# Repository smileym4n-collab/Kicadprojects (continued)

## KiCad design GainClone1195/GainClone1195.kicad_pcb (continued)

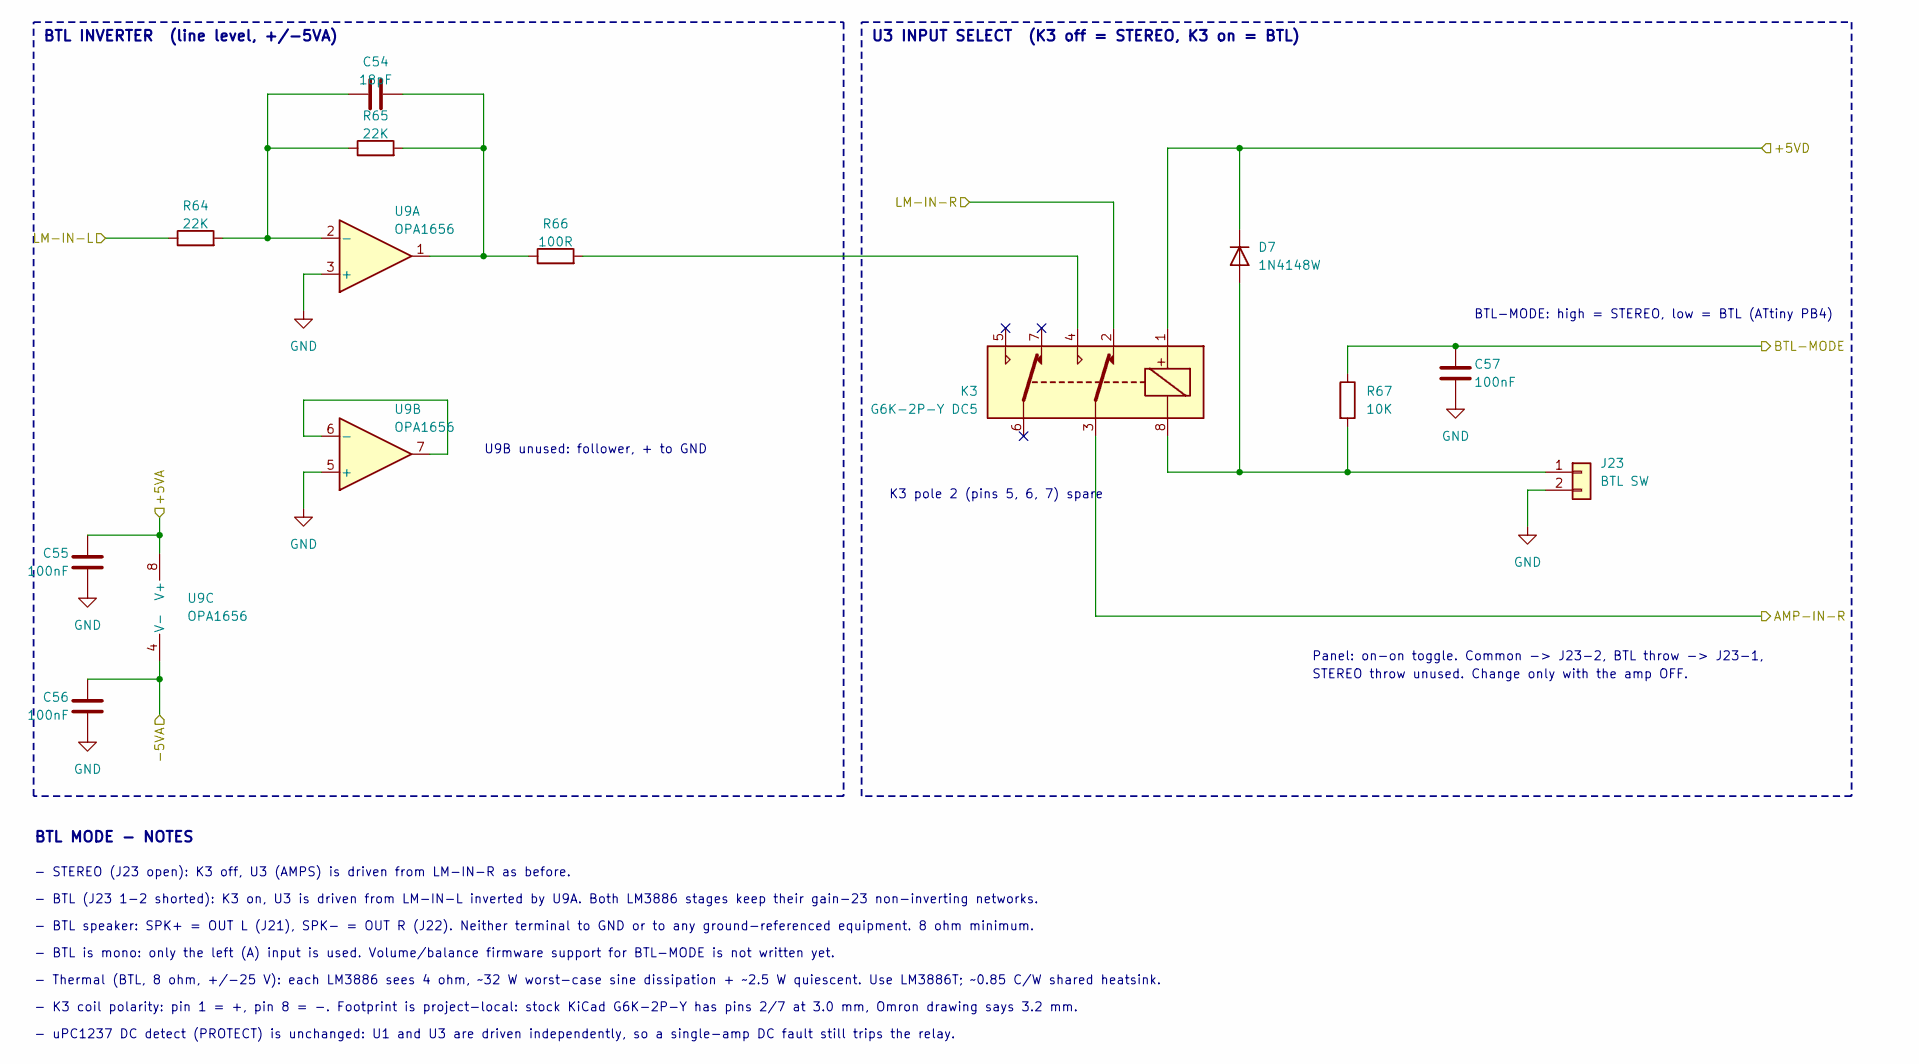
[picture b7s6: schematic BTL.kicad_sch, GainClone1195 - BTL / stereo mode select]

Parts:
C54: 18pF; C_0603_1608Metric_Pad1.08x0.95mm_HandSolder; MPN VJ0603A180JXACW1BC
C55, C56, C57: 100nF; C_0603_1608Metric_Pad1.08x0.95mm_HandSolder; MPN C0603C104M5RACTU
D7: 1N4148W; D_SOD-123; MPN 1N4148W
J23: BTL SW; JST_XH_B2B-XH-A_1x02_P2.50mm_Vertical; MPN B2B-XH-A
K3: G6K-2P-Y DC5; Relay_DPDT_Omron_G6K-2P-Y; MPN G6K-2P-Y DC5
R64, R65: 22K; R_0805_2012Metric_Pad1.20x1.40mm_HandSolder; MPN RR1220P-223-D
R66: 100R; R_0805_2012Metric_Pad1.20x1.40mm_HandSolder; MPN RC0805FR-07100RL
R67: 10K; R_0805_2012Metric_Pad1.20x1.40mm_HandSolder; MPN RC0805FR-0710KL
U9: OPA1656; SOIC-8_3.9x4.9mm_P1.27mm; MPN OPA1656IDR

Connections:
/+5VA: C55.1, U9.8 (V+); also elsewhere on the board
/+5VD: D7.1 (K), K3.1; also elsewhere on the board
/-5VA: C56.1, U9.4 (V-); also elsewhere on the board
/AMP-IN-R: K3.3; also elsewhere on the board
/BTL-MODE: C57.1, R67.1; also elsewhere on the board
/LM-IN-L: R64.1; also elsewhere on the board
/LM-IN-R: K3.2; also elsewhere on the board
GND: C55.2, C56.2, C57.2, J23.2, U9.3 (+), U9.5 (+); also elsewhere on the board
unnamed: C54.2, R65.2, R66.1, U9.1
unnamed: D7.2 (A), J23.1, K3.8, R67.2
unnamed: K3.4, R66.2
unnamed: C54.1, R64.2, R65.1, U9.2 (-)
unnamed: U9.6 (-), U9.7

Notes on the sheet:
- Thermal (BTL, 8 ohm, +/-25 V): each LM3886 sees 4 ohm, ~32 W worst-case sine dissipation + ~2.5 W quiescent. Use LM3886T; ~0.85 C/W shared heatsink.
Panel: on-on toggle. Common -> J23-2, BTL throw -> J23-1,
- K3 coil polarity: pin 1 = +, pin 8 = -. Footprint is project-local: stock KiCad G6K-2P-Y has pins 2/7 at 3.0 mm, Omron drawing says 3.2 mm.
U9B unused: follower, + to GND
BTL-MODE: high = STEREO, low = BTL (ATtiny PB4)
STEREO throw unused. Change only with the amp OFF.
- BTL speaker: SPK+ = OUT L (J21), SPK- = OUT R (J22). Neither terminal to GND or to any ground-referenced equipment. 8 ohm minimum.
K3 pole 2 (pins 5, 6, 7) spare
BTL INVERTER (line level, +/-5VA)
- STEREO (J23 open): K3 off, U3 (AMPS) is driven from LM-IN-R as before.
U3 INPUT SELECT (K3 off = STEREO, K3 on = BTL)
- BTL (J23 1-2 shorted): K3 on, U3 is driven from LM-IN-L inverted by U9A. Both LM3886 stages keep their gain-23 non-inverting networks.
- BTL is mono: only the left (A) input is used. Volume/balance firmware support for BTL-MODE is not written yet.
- uPC1237 DC detect (PROTECT) is unchanged: U1 and U3 are driven independently, so a single-amp DC fault still trips the relay.
BTL MODE - NOTES

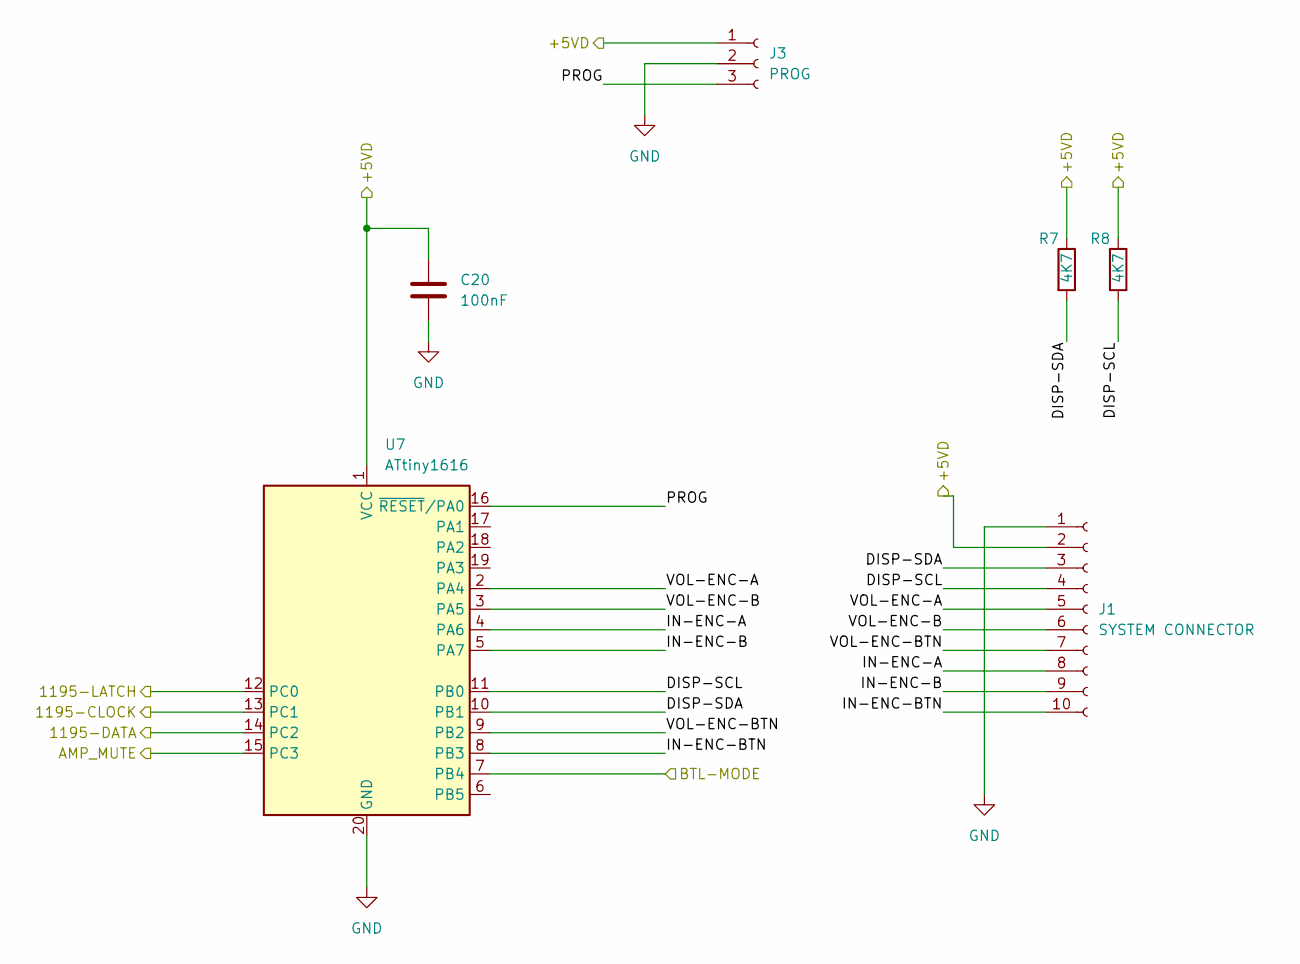
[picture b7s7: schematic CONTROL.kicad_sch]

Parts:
C20: 100nF; C_1206_3216Metric_Pad1.33x1.80mm_HandSolder
J1: SYSTEM CONNECTOR; JST_XH_B10B-XH-A_1x10_P2.50mm_Vertical
J3: PROG; PinHeader_1x03_P2.54mm_Vertical
R7, R8: 4K7; R_0805_2012Metric_Pad1.20x1.40mm_HandSolder
U7: ATtiny1616; SSOP-20_5.3x7.2mm_P0.65mm

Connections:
/+5VD: C20.1, J1.2, J3.1, R7.1, R8.1, U7.1 (VCC); also elsewhere on the board
/AMPS/AMP-MUTE: U7.15 (PC3); also elsewhere on the board
/BTL-MODE: U7.7 (PB4); also elsewhere on the board
/CONTROL/1195-CLOCK: U7.13 (PC1); also elsewhere on the board
/CONTROL/1195-DATA: U7.14 (PC2); also elsewhere on the board
/CONTROL/1195-LATCH: U7.12 (PC0); also elsewhere on the board
/CONTROL/DISP-SCL: J1.4, R8.2, U7.11 (PB0)
/CONTROL/DISP-SDA: J1.3, R7.2, U7.10 (PB1)
/CONTROL/IN-ENC-A: J1.8, U7.4 (PA6)
/CONTROL/IN-ENC-B: J1.9, U7.5 (PA7)
/CONTROL/IN-ENC-BTN: J1.10, U7.8 (PB3)
/CONTROL/PROG: J3.3, U7.16 (~RESET/PA0)
/CONTROL/VOL-ENC-A: J1.5, U7.2 (PA4)
/CONTROL/VOL-ENC-B: J1.6, U7.3 (PA5)
/CONTROL/VOL-ENC-BTN: J1.7, U7.9 (PB2)
GND: C20.2, J1.1, J3.2, U7.20 (GND); also elsewhere on the board

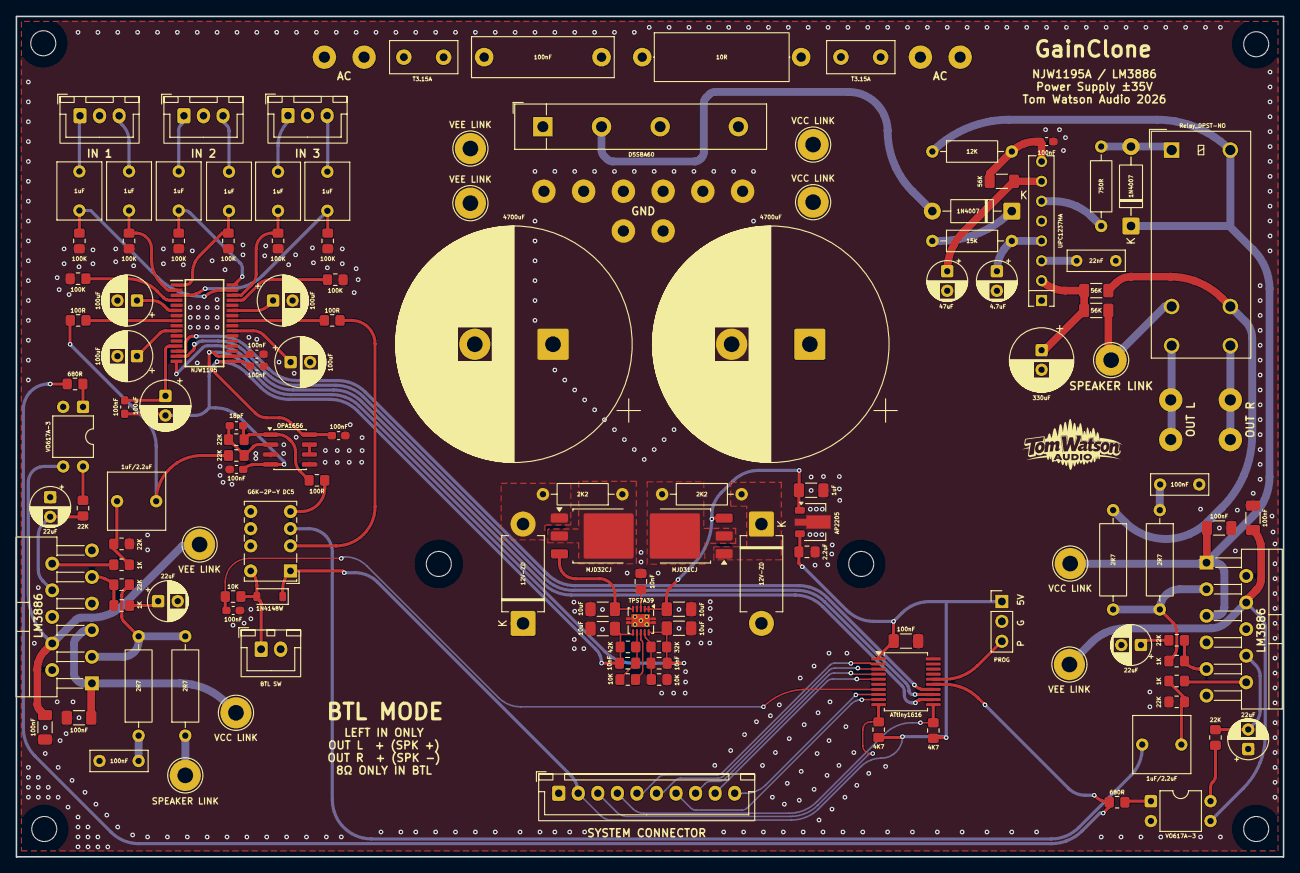
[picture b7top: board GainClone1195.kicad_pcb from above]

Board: 2 copper layers, 162.0 x 107.4 mm, 145 parts (0 on the bottom side), 97 nets.

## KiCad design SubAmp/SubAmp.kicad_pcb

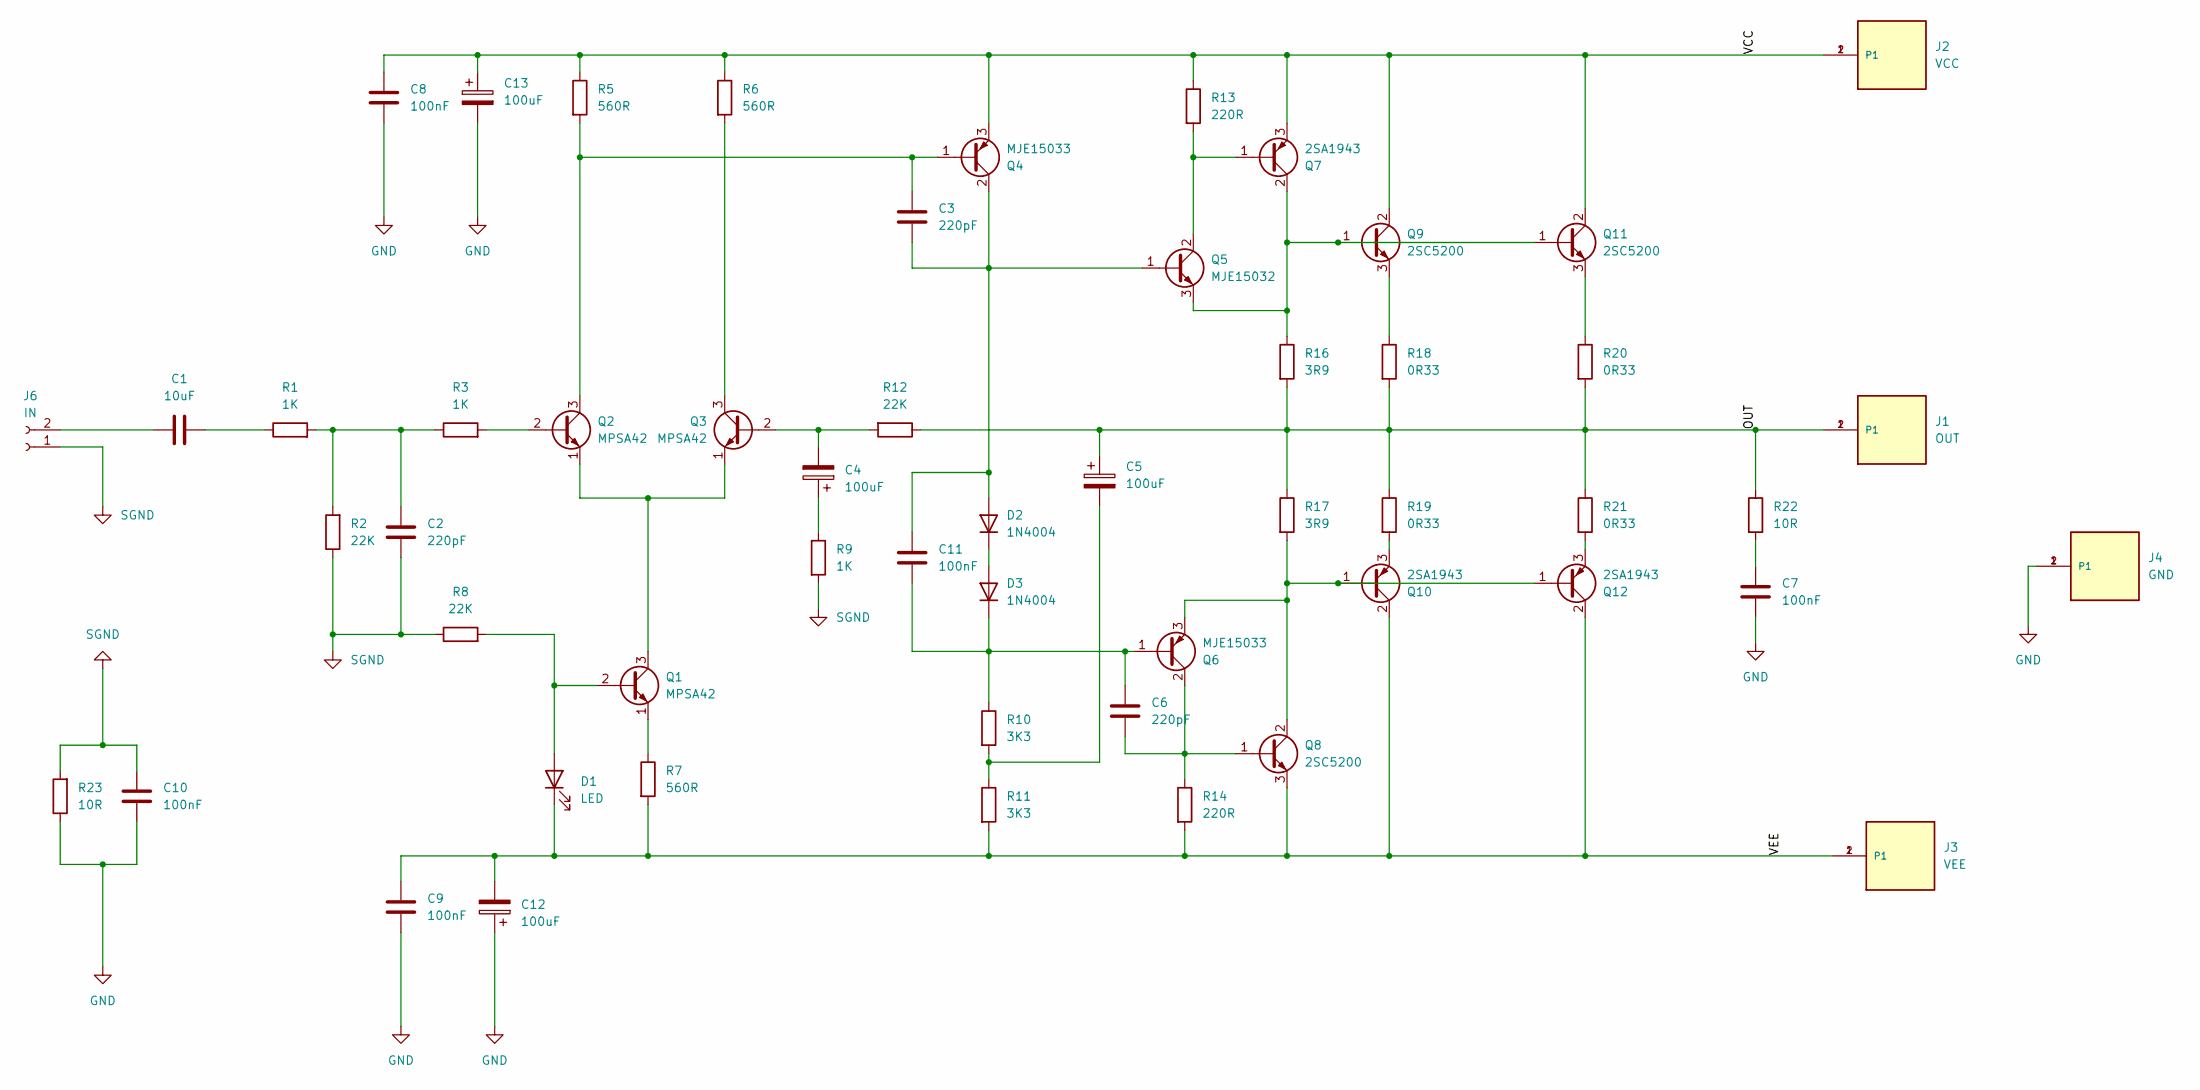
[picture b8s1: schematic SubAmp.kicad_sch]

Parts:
C1: 10uF; C_Radial_D8.0mm_H11.5mm_P3.50mm; Manufacturer_Part_Number UES1H100MPM
C2: 220pF; C_0805_2012Metric_Pad1.18x1.45mm_HandSolder; Manufacturer_Part_Number 220pfMLCCC0G50V2012
C3, C6: 220pF; C_0805_2012Metric_Pad1.18x1.45mm_HandSolder; Manufacturer_Part_Number C0805C221JAGACTU
C4: 100uF; CP_Radial_D5.0mm_P2.50mm; Manufacturer_Part_Number EEUFR1C101
C5: 100uF; CP_Radial_D8.0mm_P3.50mm; Manufacturer_Part_Number EEUFR1H101
C7: 100nF; C_Rect_L7.2mm_W2.5mm_P5.00mm_FKS2_FKP2_MKS2_MKP2; Manufacturer_Part_Number R82DC3100DQ50J
C8, C9: 100nF; C_1206_3216Metric_Pad1.33x1.80mm_HandSolder; Voltage_Rating 100; Manufacturer_Part_Number C1206C104K1RACTU
C10, C11: 100nF; C_Rect_L7.0mm_W2.5mm_P5.00mm; Manufacturer_Part_Number R82DC3100DQ50J
C12, C13: 100uF; CP_Radial_D10.0mm_P5.00mm; Manufacturer_Part_Number EEUFR2A101
D1: LED; LED_D5.0mm
D2, D3: 1N4004; D_DO-41_SOD81_P10.16mm_Horizontal; Manufacturer_Part_Number 1N4004
J1: OUT; TE_62409-1; PART_DESCRIPTION CONN QC TAB 0.250 SOLDER
J2: VCC; TE_62409-1; PART_DESCRIPTION CONN QC TAB 0.250 SOLDER
J3: VEE; TE_62409-1; PART_DESCRIPTION CONN QC TAB 0.250 SOLDER
J4: GND; TE_62409-1; PART_DESCRIPTION CONN QC TAB 0.250 SOLDER
J6: IN; JST_XH_B2B-XH-A_1x02_P2.50mm_Vertical; Manufacturer_Part_Number MC34629
Q1, Q2, Q3: MPSA42; TO-92_Wide; Manufacturer_Part_Number MPSA42
Q4, Q6: MJE15033; TO-220-3_Vertical; Manufacturer_Part_Number MJE15033G
Q5: MJE15032; TO-220-3_Vertical; Manufacturer_Part_Number MJE15032G
Q7, Q10, Q12: 2SA1943; TO-264-3_Horizontal_TabDown; Manufacturer_Part_Number 2SA1943
Q8, Q9, Q11: 2SC5200; TO-264-3_Horizontal_TabDown; Manufacturer_Part_Number 2SC5200
R1, R3, R9: 1K; R_Axial_DIN0207_L6.3mm_D2.5mm_P10.16mm_Horizontal; Manufacturer_Part_Number LR1F1K
R2, R8, R12: 22K; R_Axial_DIN0207_L6.3mm_D2.5mm_P10.16mm_Horizontal; Manufacturer_Part_Number LR1F22K
R5, R6, R7: 560R; R_Axial_DIN0207_L6.3mm_D2.5mm_P10.16mm_Horizontal; Manufacturer_Part_Number LR1F560R
R10, R11: 3K3; R_Axial_DIN0207_L6.3mm_D2.5mm_P10.16mm_Horizontal; Manufacturer_Part_Number LR1F3K3
R13, R14: 220R; R_Axial_DIN0207_L6.3mm_D2.5mm_P10.16mm_Horizontal; Manufacturer_Part_Number LR1F220R
R16, R17: 3R9; R_Axial_DIN0617_L17.0mm_D6.0mm_P25.40mm_Horizontal; Manufacturer_Part_Number Multicomp Pro
R18, R19, R20, R21: 0R33; R_Axial_DIN0617_L17.0mm_D6.0mm_P25.40mm_Horizontal; Manufacturer_Part_Number Multicomp Pro
R22, R23: 10R; R_Axial_DIN0414_L11.9mm_D4.5mm_P15.24mm_Horizontal; Manufacturer_Part_Number RSMF2JT10R0

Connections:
/OUT: C5.1, J1.1, J1.2 (P1), R12.1, R16.2, R17.1, R18.2, R19.1, R20.2, R21.1, R22.1
/VCC: C8.1, C13.1, J2.1, J2.2 (P1), Q4.3 (E), Q7.3 (E), Q9.2 (C), Q11.2 (C), R5.1, R6.1, R13.1
/VEE: C9.1, C12.2, D1.1 (K), J3.1, J3.2 (P1), Q8.3 (E), Q10.2 (C), Q12.2 (C), R7.2, R11.2, R14.2
GND: C7.2, C8.2, C9.2, C10.2, C12.1, C13.2, J4.1, J4.2 (P1), R23.1
unnamed: C1.2, R1.1
unnamed: C2.1, R1.2, R2.2, R3.1
unnamed: C4.1, R9.1
unnamed: C5.2, R10.2, R11.1
unnamed: C7.1, R22.2
unnamed: D1.2 (A), Q1.2 (B), R8.2
unnamed: C3.2, C11.1, D2.2 (A), Q4.2 (C), Q5.1 (B)
unnamed: D2.1 (K), D3.2 (A)
unnamed: C6.1, C11.2, D3.1 (K), Q6.1 (B), R10.1
unnamed: C1.1, J6.2
unnamed: Q1.3 (C), Q2.1 (E), Q3.1 (E)
unnamed: Q1.1 (E), R7.1
unnamed: Q2.2 (B), R3.2
unnamed: C3.1, Q2.3 (C), Q4.1 (B), R5.2
unnamed: C4.2, Q3.2 (B), R12.2
unnamed: Q3.3 (C), R6.2
unnamed: Q5.2 (C), Q7.1 (B), R13.2
unnamed: C6.2, Q6.2 (C), Q8.1 (B), R14.1
unnamed: Q9.3 (E), R18.1
unnamed: Q6.3 (E), Q8.2 (C), Q10.1 (B), Q12.1 (B), R17.2
unnamed: Q10.3 (E), R19.2
unnamed: Q5.3 (E), Q7.2 (C), Q9.1 (B), Q11.1 (B), R16.1
unnamed: Q11.3 (E), R20.1
unnamed: Q12.3 (E), R21.2
SGND: C2.2, C10.1, J6.1, R2.1, R8.1, R9.2, R23.2

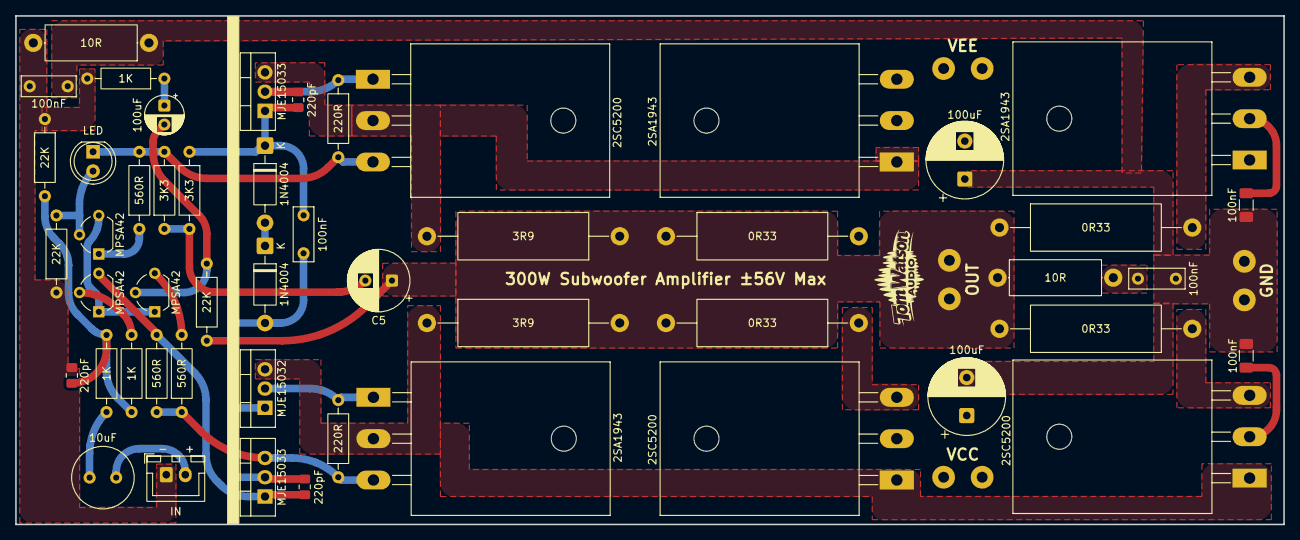
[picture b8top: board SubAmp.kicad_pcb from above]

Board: 2 copper layers, 167.1 x 67.0 mm, 54 parts (0 on the bottom side), 29 nets.

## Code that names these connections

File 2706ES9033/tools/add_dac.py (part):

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    W((px, RAIL), (px, py))
RC("C21", "10u", X0 - 38.1, RAIL + 3.81); gnd(X0 - 38.1, RAIL + 7.62)
pwrflag(X0 - 22.86, RAIL)
RC("C22", "100n", X0 - 27.94, RAIL + 3.81); gnd(X0 - 27.94, RAIL + 7.62)    # AVDD pin 1
RC("C23", "1u", X0 - 17.78, RAIL + 3.81); gnd(X0 - 17.78, RAIL + 7.62)      # AVDD pin 1
RC("C24", "1u", X0 + 17.78, RAIL + 3.81); gnd(X0 + 17.78, RAIL + 7.62)      # VCCA pin 4
RC("C25", "1u", X0 + 27.94, RAIL + 3.81); gnd(X0 + 27.94, RAIL + 7.62)      # AVCC_3V3 pin 9
RC("C26", "100n", X0 + 38.1, RAIL + 3.81); gnd(X0 + 38.1, RAIL + 7.62)      # AVCC_CP pin 17
RC("C27", "1u", X0 + 48.26, RAIL + 3.81); gnd(X0 + 48.26, RAIL + 7.62)      # AVCC_CP pin 17
T("Place at pins: C22,C23 -> pin 1 AVDD;  C24 -> pin 4 VCCA;  C25 -> pin 9 AVCC_3V3;  C26,C27 -> pin 17 AVCC_CP",
  X0 - 30.48, RAIL - 8.89, 1.27)

# ---------------- U2 left side: I2S, control, straps ----------------
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    px, py = P("U3", n)
    W((px, py), (px + 7.62, py))
    L(net, px + 7.62, py)
ncs.append(P("U3", "7"))                 # PA3 spare
# PA6: PCM2706 3V3 rail sense through R25
px, py = P("U3", "2")
sx = px + 12.7
W((px, py), (sx, py), (sx, py + 3.81))
RC("R25", "10k", sx, py + 7.62)
W((sx, py + 11.43), (sx, py + 13.97))
L("3V3", sx, py + 13.97, 270)
# PA7: DAC_EN with pull-down
px, py = P("U3", "3")
dx = px + 2.54
W((px, py), (dx, py), (dx, py + 3.81))
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RC("R24", "100k", dx, py + 7.62)
gnd(dx, py + 11.43)
T("CONTROL", AX - 45.72, AY - 33.02, 2.54, True)
T("U3 holds DAC_EN low until the PCM2706 3V3 rail is up and MCLK is stable,\nthen CHIP_EN high, wait 100 ms, clock setup at 0x98, then config at 0x90.\nPA6 senses the PCM2706 rail (3V3) via R25.  PA3 spare.",
  AX - 22.86, AY + 33.02, 1.27)
# I2C pull-ups
for ref, x, net in (("R22", AX + 25.4, "I2C_SDA"), ("R23", AX + 33.02, "I2C_SCL")):
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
